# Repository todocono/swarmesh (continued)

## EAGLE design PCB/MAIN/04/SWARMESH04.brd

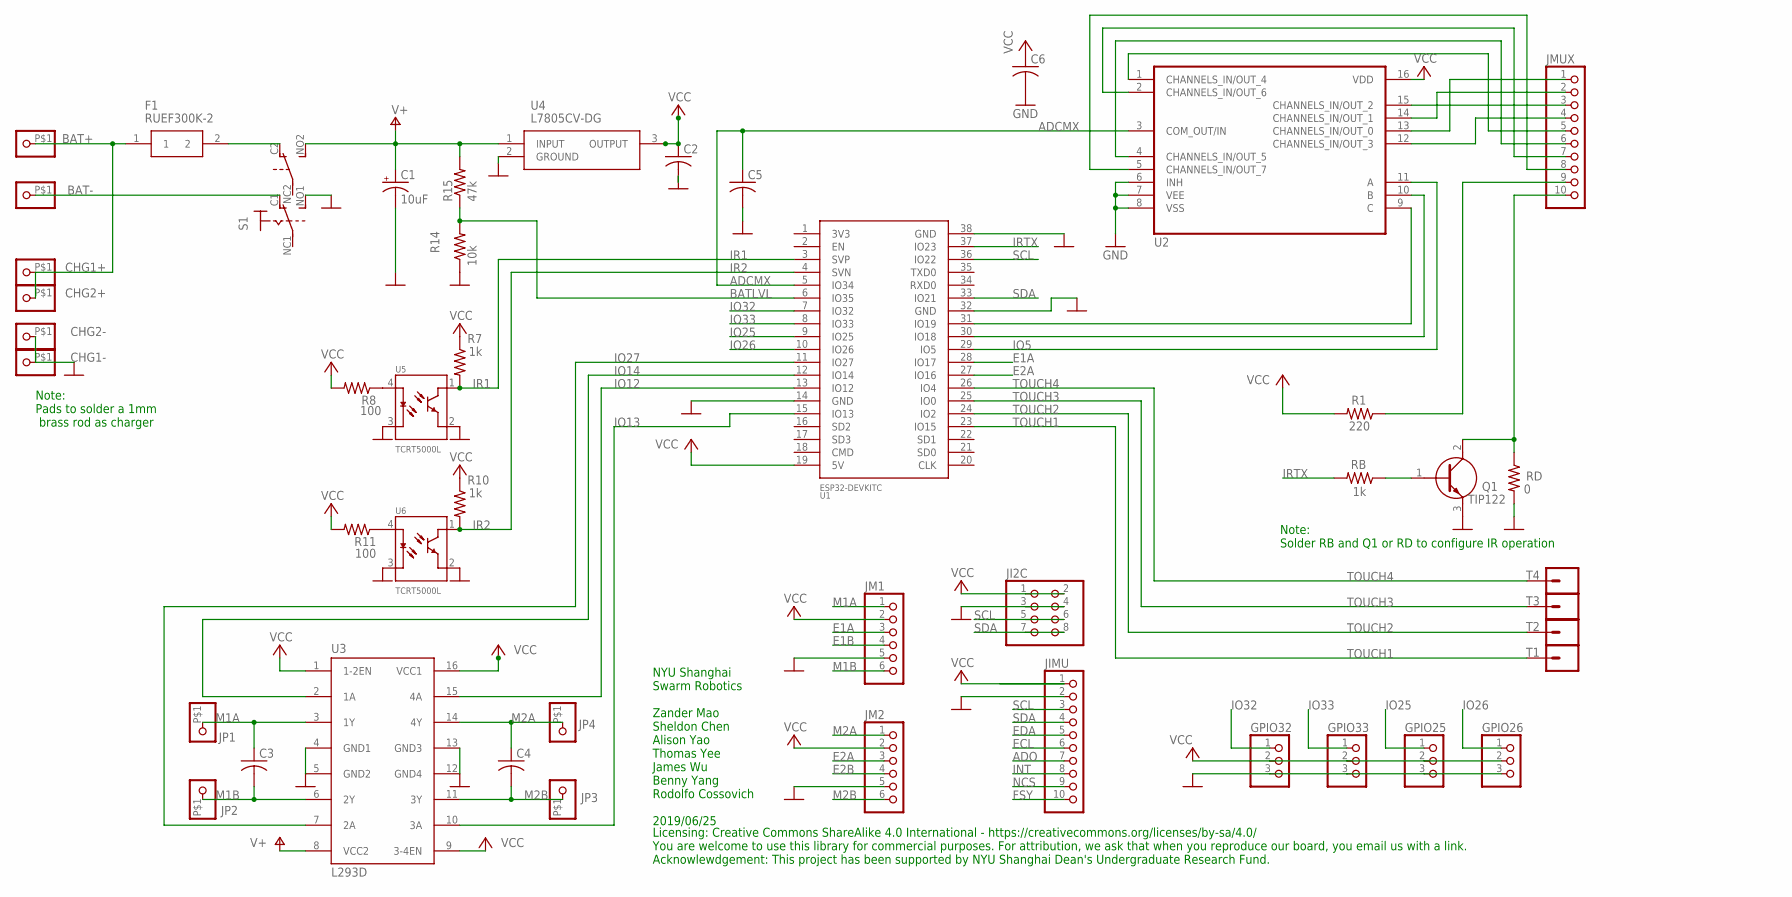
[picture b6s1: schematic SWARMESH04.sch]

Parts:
BAT+: PINHD-1X1-BIGPOGO; 1X1-BIGPOGO
BAT-: PINHD-1X1-BIGPOGO; 1X1-BIGPOGO
C1: 10uF; E2-5
C2, C5: C-US025-030X050; C025-030X050
C3, C4, C6: C-US025-025X050; C025-025X050
CHG1+, CHG1-, CHG2+, CHG2-: PINHD-1X1-BIGPOGO; 1X1-BIGPOGO
F1: RUEF300K-2; RUEF300K2
GPIO25, GPIO26, GPIO32, GPIO33: PINHD-1X3; 1X03
JI2C: PINHD-2X4; 2X04
JIMU: PINHD-1X10; 1X10-BIG
JM1, JM2: PINHD-1X6; 1X06
JMUX: PINHD-1X10; 1X10-BIG
JP1, JP2, JP3, JP4: PINHD-1X1-BIGPOGO; 1X1-BIGPOGO
Q1: TIP122; TO270P460X1020X2008-3P
R1: 220; 0207/9
R7, R10: 1k; 0207/9
R8, R11: 100; 0207/9
R14: 10k; 0207/9
R15: 47k; 0207/9
RB: 1k; 0207/9
RD: 0; 0207/9
S1: SWITCH_320-938; PS22F03
T1, T2, T3, T4: CONN_01SPRING-CONN; SPRING-CONNECTOR
U1: ESP32DEVKITC; ESP32-DEVKITC
U2: CD4051BEE4; CD4051BEE4DIP
U3: L293D; DIL16
U4: L7805CV-DG; TO270P460X1020X2008-3P
U5, U6: TCRT5000L; XDCR_TCRT5000L

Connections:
ADCMX: C5.1, U1.5 (IO34), U2.3 (COM_OUT/IN)
ADO: JIMU.7
BATLVL: R14.2, R15.1, U1.6 (IO35)
E1A: JM1.3, U1.28 (IO17)
E1B: JM1.4
E2A: JM2.3, U1.27 (IO16)
E2B: JM2.4
ECL: JIMU.6
EDA: JIMU.5
FSY: JIMU.10
GND: C1.-, C2.2, C5.2, C6.2, CHG1-.P$1, CHG2-.P$1, GPIO25.3, GPIO26.3, GPIO32.3, GPIO33.3, JI2C.3, JI2C.4, JIMU.2, JM1.5, JM2.5, Q1.3 (E), R14.1, RD.2, S1.NO1 (S), U1.14 (GND), U1.32 (GND), U1.38 (GND), U2.6 (INH), U2.7 (VEE), U2.8 (VSS), U3.4 (GND1), U3.5 (GND2), U3.12 (GND4), U3.13 (GND3), U4.2 (GROUND), U5.2 (E), U5.3 (C), U6.2 (E), U6.3 (C)
INT: JIMU.8
IO5: U1.29 (IO5), U2.11 (A)
IO12: U1.13 (IO12), U3.15 (4A)
IO13: U1.15 (IO13), U3.10 (3A)
IO14: U1.12 (IO14), U3.2 (1A)
IO25: GPIO25.1, U1.9 (IO25)
IO26: GPIO26.1, U1.10 (IO26)
IO27: U1.11 (IO27), U3.7 (2A)
IO32: GPIO32.1, U1.7 (IO32)
IO33: GPIO33.1, U1.8 (IO33)
IR1: R7.2, U1.3 (SVP), U5.1 (CO)
IR2: R10.2, U1.4 (SVN), U6.1 (CO)
IRTX: RB.2, U1.37 (IO23)
M1A: C3.1, JM1.1, JP1.P$1, U3.3 (1Y)
M1B: C3.2, JM1.6, JP2.P$1, U3.6 (2Y)
M2A: C4.1, JM2.1, JP4.P$1, U3.14 (4Y)
M2B: C4.2, JM2.6, JP3.P$1, U3.11 (3Y)
unnamed: Q1.1 (B), RB.1
unnamed: F1.2, S1.C2 (O)
unnamed: BAT-.P$1, S1.C1 (O)
unnamed: JMUX.6, U2.4 (CHANNELS_IN/OUT_5)
unnamed: U1.30 (IO18), U2.10 (B)
unnamed: U1.31 (IO19), U2.9 (C)
unnamed: R11.1, U6.4 (A)
unnamed: R8.1, U5.4 (A)
unnamed: JMUX.5, U2.1 (CHANNELS_IN/OUT_4)
unnamed: JMUX.7, U2.2 (CHANNELS_IN/OUT_6)
unnamed: JMUX.8, U2.5 (CHANNELS_IN/OUT_7)
unnamed: BAT+.P$1, CHG1+.P$1, CHG2+.P$1, F1.1
unnamed: JMUX.9, R1.1
unnamed: JMUX.10, Q1.2 (C), RD.1
unnamed: JMUX.1, U2.13 (CHANNELS_IN/OUT_0)
unnamed: JMUX.2, U2.14 (CHANNELS_IN/OUT_1)
unnamed: JMUX.4, U2.12 (CHANNELS_IN/OUT_3)
unnamed: JMUX.3, U2.15 (CHANNELS_IN/OUT_2)
NCS: JIMU.9
SCL: JI2C.5, JI2C.6, JIMU.3, U1.36 (IO22)
SDA: JI2C.7, JI2C.8, JIMU.4, U1.33 (IO21)
TOUCH1: T1.P$2, U1.23 (IO15)
TOUCH2: T2.P$2, U1.24 (IO2)
TOUCH3: T3.P$2, U1.25 (IO0)
TOUCH4: T4.P$2, U1.26 (IO4)
V+: C1.+, R15.2, S1.NO2 (S), U3.8 (VCC2), U4.1 (INPUT)
VCC: C2.1, C6.1, GPIO25.2, GPIO26.2, GPIO32.2, GPIO33.2, JI2C.1, JI2C.2, JIMU.1, JM1.2, JM2.2, R1.2, R7.1, R8.2, R10.1, R11.2, U1.19 (5V), U2.16 (VDD), U3.1 (1-2EN), U3.9 (3-4EN), U3.16 (VCC1), U4.3 (OUTPUT)

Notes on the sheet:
NYU Shanghai Swarm Robotics Zander Mao Sheldon Chen Alison Yao Thomas Yee James Wu Benny Yang Rodolfo Cossovich 2019/06/25
Licensing: Creative Commons ShareAlike 4.0 International - https://creativecommons.org/licenses/by-sa/4.0/ You are welcome to use this library for commercial purposes. For attribution, we ask that when you reproduce our board, you email us with a link. Acknowlewdgement: This project has been suppor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
Note: Solder RB and Q1 or RD to configure IR operation
Note: Pads to solder a 1mm brass rod as charger

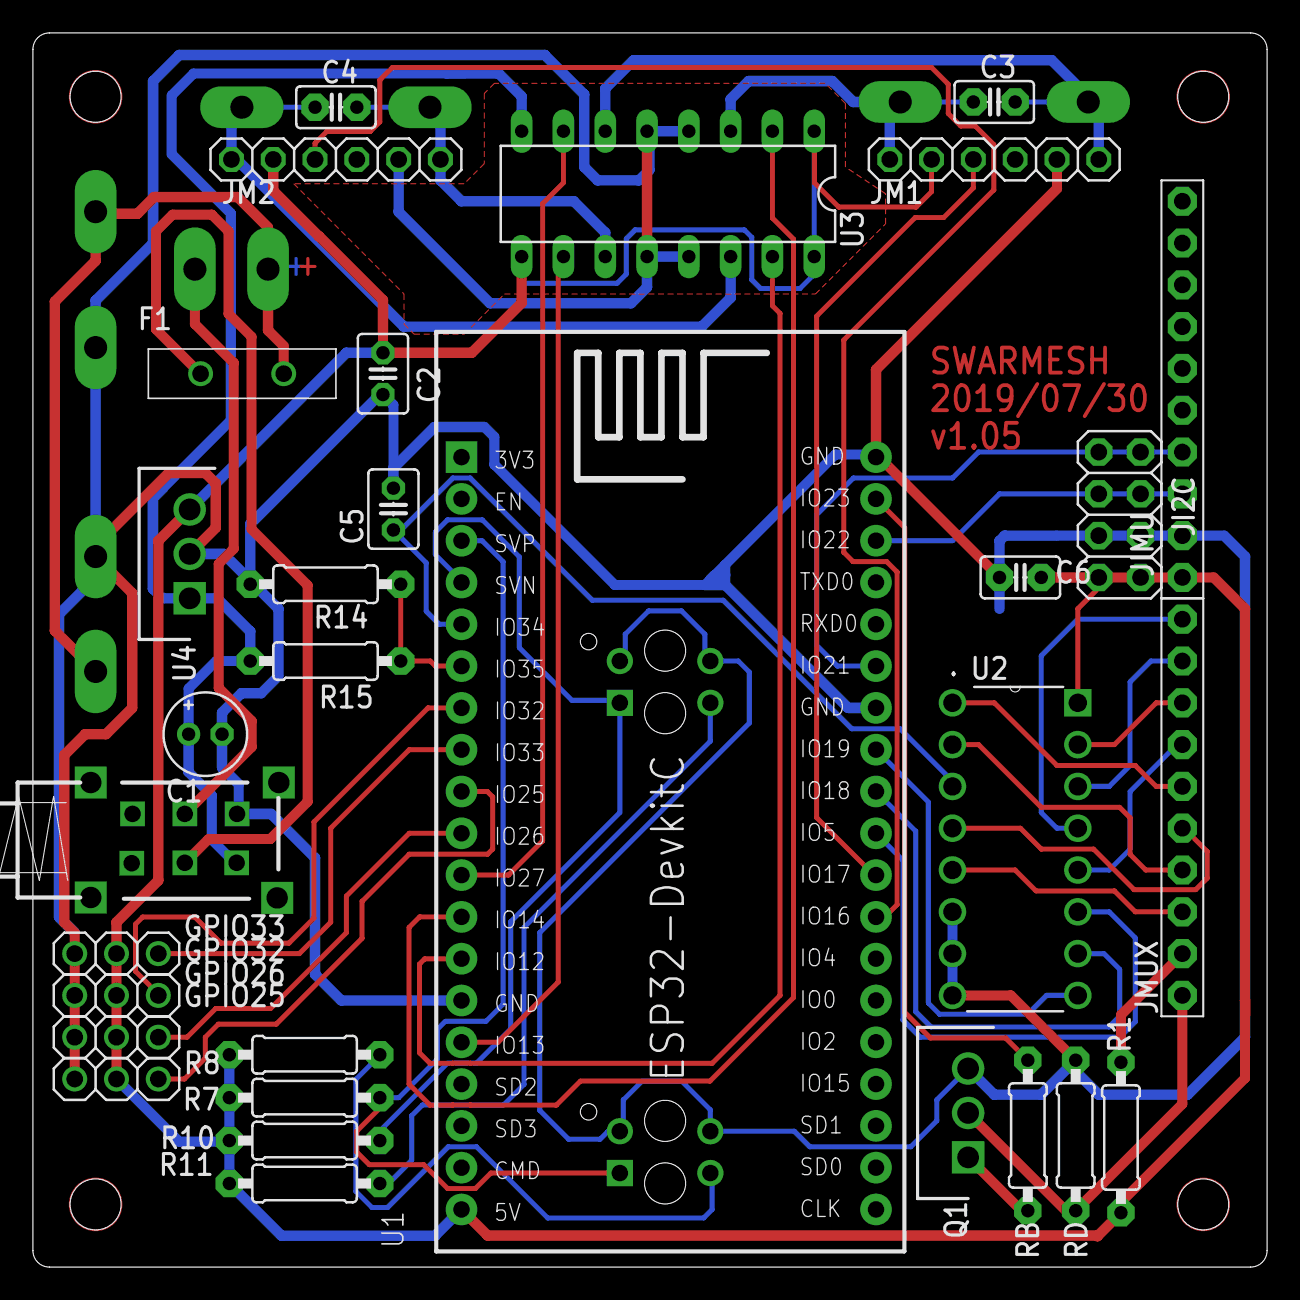
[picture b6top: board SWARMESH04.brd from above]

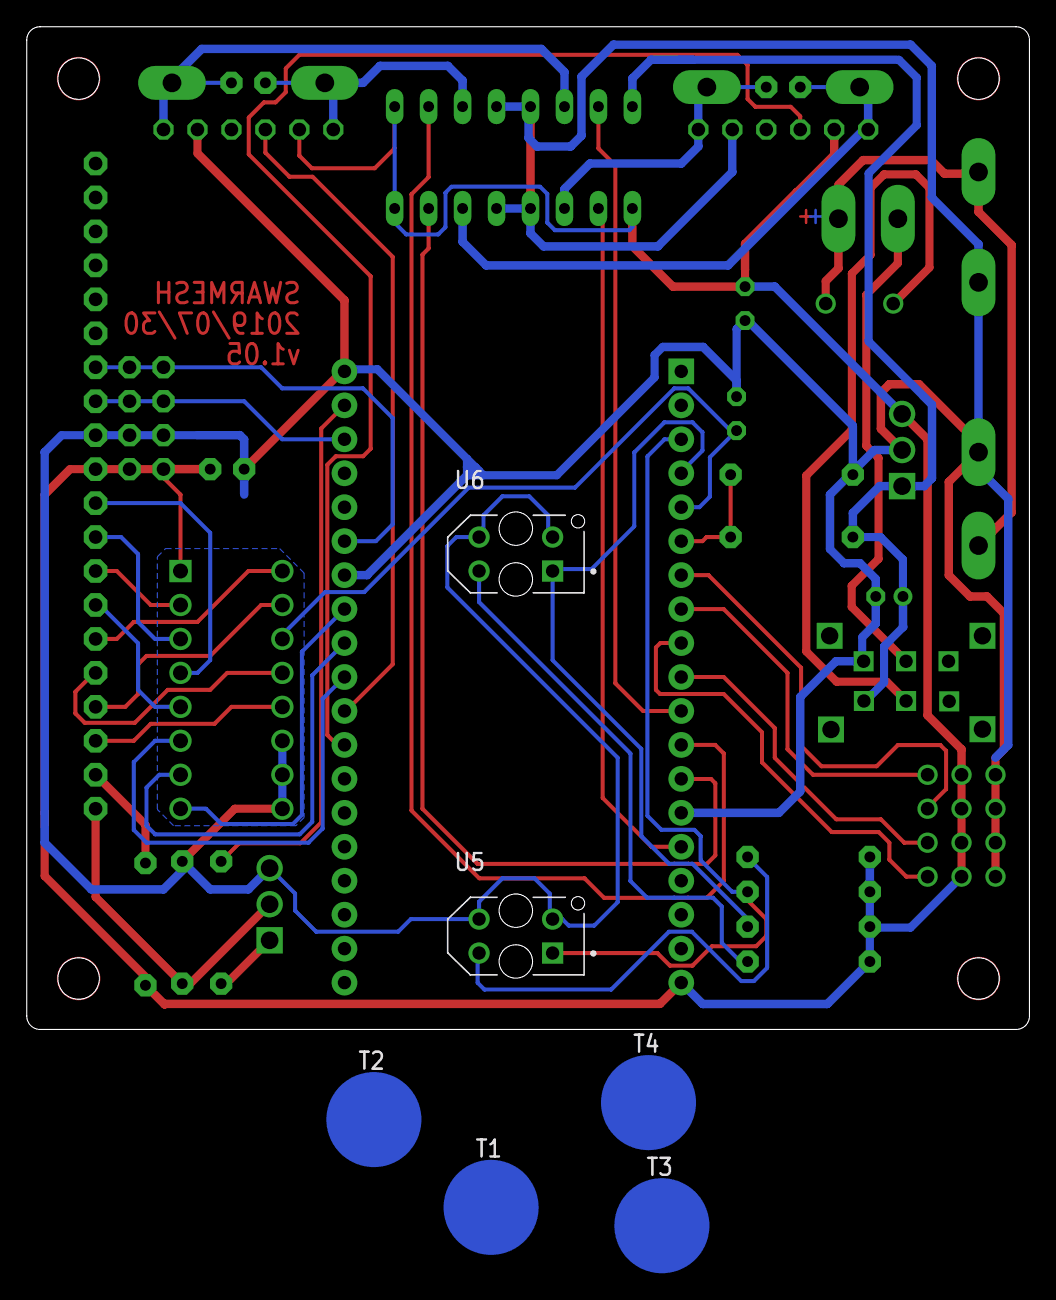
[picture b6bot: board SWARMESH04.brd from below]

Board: 2 copper layers, 75.0 x 75.0 mm, 47 parts (7 on the bottom side), 47 nets.

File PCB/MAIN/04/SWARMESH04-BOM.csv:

"Part";"Value";"Device";"Package";"Description";"ALLIED_NUMBER";"ALLIED_PRICE-STOCK";"AVAILABILITY";"DESCRIPTION";"HEIGHT";"MANUFACTURER_NAME";"MANUFACTURER_PART_NUMBER";"MF";"MOUSER_PART_NUMBER";"MOUSER_PRICE-STOCK";"MP";"MPN";"OC_FARNELL";"OC_NEWARK";"PACKAGE";"PRICE";"RS_PART_NUMBER";"RS_PRICE-STOCK";"SF_ID";
"BAT+";"";"PINHD-1X1-BIGPOGO";"1X1-BIGPOGO";"Pin header 1x1 for 0.1" spacing";"";"";"";"";"";"";"";"";"";"";"";"";"";"";"";"";"";"";"";
"BAT-";"";"PINHD-1X1-BIGPOGO";"1X1-BIGPOGO";"Pin header 1x1 for 0.1" spacing";"";"";"";"";"";"";"";"";"";"";"";"";"";"";"";"";"";"";"";
"C1";"10uF";"CPOL-USE2-5";"E2-5";"POLARIZED CAPACITOR, American symbol";"";"";"";"";"";"";"";"";"";"";"";"";"";"";"";"";"";"";"";
"C2";"";"C-US025-030X050";"C025-030X050";"CAPACITOR, American symbol";"";"";"";"";"";"";"";"";"";"";"";"";"";"";"";"";"";"";"";
"C3";"";"C-US025-025X050";"C025-025X050";"CAPACITOR, American symbol";"";"";"";"";"";"";"";"";"";"";"";"";"";"";"";"";"";"";"";
"C4";"";"C-US025-025X050";"C025-025X050";"CAPACITOR, American symbol";"";"";"";"";"";"";"";"";"";"";"";"";"";"";"";"";"";"";"";
"C5";"";"C-US025-030X050";"C025-030X050";"CAPACITOR, American symbol";"";"";"";"";"";"";"";"";"";"";"";"";"";"";"";"";"";"";"";
"C6";"";"C-US025-025X050";"C025-025X050";"CAPACITOR, American symbol";"";"";"";"";"";"";"";"";"";"";"";"";"";"";"";"";"";"";"";
"CHG1+";"";"PINHD-1X1-BIGPOGO";"1X1-BIGPOGO";"Pin header 1x1 for 0.1" spacing";"";"";"";"";"";"";"";"";"";"";"";"";"";"";"";"";"";"";"";
"CHG1-";"";"PINHD-1X1-BIGPOGO";"1X1-BIGPOGO";"Pin header 1x1 for 0.1" spacing";"";"";"";"";"";"";"";"";"";"";"";"";"";"";"";"";"";"";"";
"CHG2+";"";"PINHD-1X1-BIGPOGO";"1X1-BIGPOGO";"Pin header 1x1 for 0.1" spacing";"";"";"";"";"";"";"";"";"";"";"";"";"";"";"";"";"";"";"";
"CHG2-";"";"PINHD-1X1-BIGPOGO";"1X1-BIGPOGO";"Pin header 1x1 for 0.1" spacing";"";"";"";"";"";"";"";"";"";"";"";"";"";"";"";"";"";"";"";
"F1";"RUEF300K-2";"RUEF300K-2";"RUEF300K2";"TE CONNECTIVITY / RAYCHEM - RUEF300K-2 - RESETTABLE FUSE, PTC, 30V, 3A, RADIAL";"";"";"";"TE CONNECTIVITY / RAYCHEM - RUEF300K-2 - RESETTABLE FUSE, PTC, 30V, 3A, RADIAL";"16.5mm";"TE CONNECTIVITY / RAYCHEM";"RUEF300K-2";"";"";"";"";"";"";"";"";"";"";"";"";
"GPIO25";"";"PINHD-1X3";"1X03";"PIN HEADER";"";"";"";"";"";"";"";"";"";"";"";"";"";"";"";"";"";"";"";
"GPIO26";"";"PINHD-1X3";"1X03";"PIN HEADER";"";"";"";"";"";"";"";"";"";"";"";"";"";"";"";"";"";"";"";
"GPIO32";"";"PINHD-1X3";"1X03";"PIN HEADER";"";"";"";"";"";"";"";"";"";"";"";"";"";"";"";"";"";"";"";
"GPIO33";"";"PINHD-1X3";"1X03";"PIN HEADER";"";"";"";"";"";"";"";"";"";"";"";"";"";"";"";"";"";"";"";
"JI2C";"";"PINHD-2X4";"2X04";"PIN HEADER";"";"";"";"";"";"";"";"";"";"";"";"";"";"";"";"";"";"";"";
"JIMU";"PINHD-1X10";"PINHD-1X10";"1X10-BIG";"Pin header 1x10 0.1" spacing";"";"";"";"";"";"";"";"";"";"";"";"";"";"";"";"";"";"";"";
"JM1";"";"PINHD-1X6";"1X06";"PIN HEADER";"";"";"";"";"";"";"";"";"";"";"";"";"";"";"";"";"";"";"";
"JM2";"";"PINHD-1X6";"1X06";"PIN HEADER";"";"";"";"";"";"";"";"";"";"";"";"";"";"";"";"";"";"";"";
"JMUX";"PINHD-1X10";"PINHD-1X10";"1X10-BIG";"Pin header 1x10 0.1" spacing";"";"";"";"";"";"";"";"";"";"";"";"";"";"";"";"";"";"";"";
"JP1";"";"PINHD-1X1-BIGPOGO";"1X1-BIGPOGO";"Pin header 1x1 for 0.1" spacing";"";"";"";"";"";"";"";"";"";"";"";"";"";"";"";"";"";"";"";
"JP2";"";"PINHD-1X1-BIGPOGO";"1X1-BIGPOGO";"Pin header 1x1 for 0.1" spacing";"";"";"";"";"";"";"";"";"";"";"";"";"";"";"";"";"";"";"";
"JP3";"";"PINHD-1X1-BIGPOGO";"1X1-BIGPOGO";"Pin header 1x1 for 0.1" spacing";"";"";"";"";"";"";"";"";"";"";"";"";"";"";"";"";"";"";"";
"JP4";"";"PINHD-1X1-BIGPOGO";"1X1-BIGPOGO";"Pin header 1x1 for 0.1" spacing";"";"";"";"";"";"";"";"";"";"";"";"";"";"";"";"";"";"";"";
"Q1";"TIP122";"TIP122";"TO270P460X1020X2008-3P";"TIP122, Darlington Transistor, NPN 8 A 100 V HFE:1000, 3-Pin, TO-220";"";"";"";"TIP122, Darlington Transistor, NPN 8 A 100 V HFE:1000, 3-Pin, TO-220";"4.6mm";"STMicroelectronics";"TIP122";"";"511-TIP122";"https://www.mouser.com/Search/Refine.aspx?Keyword=511-TIP122";"";"";"";"";"";"";"";"";"";
"R1";"220";"R-US_0207/9";"0207/9";"RESISTOR, American symbol";"";"";"";"";"";"";"";"";"";"";"";"";"";"";"";"";"";"";"";
"R7";"1k";"R-US_0207/9";"0207/9";"RESISTOR, American symbol";"";"";"";"";"";"";"";"";"";"";"";"";"";"";"";"";"";"";"";
"R8";"100";"R-US_0207/9";"0207/9";"RESISTOR, American symbol";"";"";"";"";"";"";"";"";"";"";"";"";"";"";"";"";"";"";"";
"R10";"1k";"R-US_0207/9";"0207/9";"RESISTOR, American symbol";"";"";"";"";"";"";"";"";"";"";"";"";"";"";"";"";"";"";"";
"R11";"100";"R-US_0207/9";"0207/9";"RESISTOR, American symbol";"";"";"";"";"";"";"";"";"";"";"";"";"";"";"";"";"";"";"";
"R14";"10k";"R-US_0207/9";"0207/9";"RESISTOR, American symbol";"";"";"";"";"";"";"";"";"";"";"";"";"";"";"";"";"";"";"";
"R15";"47k";"R-US_0207/9";"0207/9";"RESISTOR, American symbol";"";"";"";"";"";"";"";"";"";"";"";"";"";"";"";"";"";"";"";
"RB";"1k";"R-US_0207/9";"0207/9";"RESISTOR, American symbol";"";"";"";"";"";"";"";"";"";"";"";"";"";"";"";"";"";"";"";
"RD";"0";"R-US_0207/9";"0207/9";"RESISTOR, American symbol";"";"";"";"";"";"";"";"";"";"";"";"";"";"";"";"";"";"";"";
"S1";"";"SWITCH_320-938";"PS22F03";"TOGGLE SWITCH";"";"";"";"";"";"";"";"";"";"";"";"";"";"";"";"";"";"";"";
"T1";"";"CONN_01SPRING-CONN";"SPRING-CONNECTOR";"Single connection point. Often used as Generic Header-pin footprint for 0.1 inch spaced/style header connections";"";"";"";"";"";"";"";"";"";"";"";"";"";"";"";"";"";"";"PRT-11822";
"T2";"";"CONN_01SPRING-CONN";"SPRING-CONNECTOR";"Single connection point. Often used as Generic Header-pin footprint for 0.1 inch spaced/style header connections";"";"";"";"";"";"";"";"";"";"";"";"";"";"";"";"";"";"";"PRT-11822";
"T3";"";"CONN_01SPRING-CONN";"SPRING-CONNECTOR";"Single connection point. Often used as Generic Header-pin footprint for 0.1 inch spaced/style header connections";"";"";"";"";"";"";"";"";"";"";"";"";"";"";"";"";"";"";"PRT-11822";
"T4";"";"CONN_01SPRING-CONN";"SPRING-CONNECTOR";"Single connection point. Often used as Generic Header-pin footprint for 0.1 inch spaced/style header connections";"";"";"";"";"";"";"";"";"";"";"";"";"";"";"";"";"";"";"PRT-11822";
"U1";"ESP32DEVKITC";"ESP32DEVKITC";"ESP32-DEVKITC";"";"";"";"";"";"";"";"";"";"";"";"";"";"";"";"";"";"";"";"";
"U2";"CD4051BEE4";"CD4051BEE4";"CD4051BEE4DIP";"Multiplexer 8pin ADC/DAC";"";"";"";"";"";"";"";"";"";"";"";"";"";"";"";"";"";"";"";
"U3";"L293D";"L293D";"DIL16";"PUSH-PULL 4 CHANNEL DRIVER";"";"";"";"";"";"";"";"";"";"";"";"L293D";"9589619";"56P8249";"";"";"";"";"";
"U4";"L7805CV-DG";"L7805CV-DG";"TO270P460X1020X2008-3P";"Voltage Regulator 5V 4% 1.5A TO220 L7805CV-DG, Linear Voltage Regulator, Current Limit, Shut-Down 1.5A 5 V, 3-Pin TO220";"70390055";"http://www.alliedelec.com/stmicroelectronics-l7805cv-dg/70390055/";"";"Voltage Regulator 5V 4% 1.5A TO220 L7805CV-DG, Linear Voltage Regulator, Current Limit, Shut-Down 1.5A 5 V, 3-Pin TO220";"4.6mm";"STMicroelectronics";"L7805CV-DG";"";"511-L7805CV-DG";"https://www.mouser.com/Search/Refine.aspx?Keyword=511-L7805CV-DG";"";"";"";"";"";"";"7931346P";"http://uk.rs-online.com/web/p/products/7931346P";"";
"U5";"TCRT5000L";"TCRT5000L";"XDCR_TCRT5000L";"TCRT5000 Series 940 nm 100 mA 60 mA Transistor Output Reflective Optical Sensor";"";"";"Unavailable";" TCRT5000 Series 940 nm 100 mA 60 mA Transistor Output Reflective Optical Sensor ";"";"";"";"Vishay Semiconductor";"";"";"TCRT5000L";"";"";"";"PCB Mount Vishay";"None";"";"";"";
"U6";"TCRT5000L";"TCRT5000L";"XDCR_TCRT5000L";"TCRT5000 Series 940 nm 100 mA 60 mA Transistor Output Reflective Optical Sensor";"";"";"Unavailable";" TCRT5000 Series 940 nm 100 mA 60 mA Transistor Output Reflective Optical Sensor ";"";"";"";"Vishay Semiconductor";"";"";"TCRT5000L";"";"";"";"PCB Mount Vishay";"None";"";"";"";

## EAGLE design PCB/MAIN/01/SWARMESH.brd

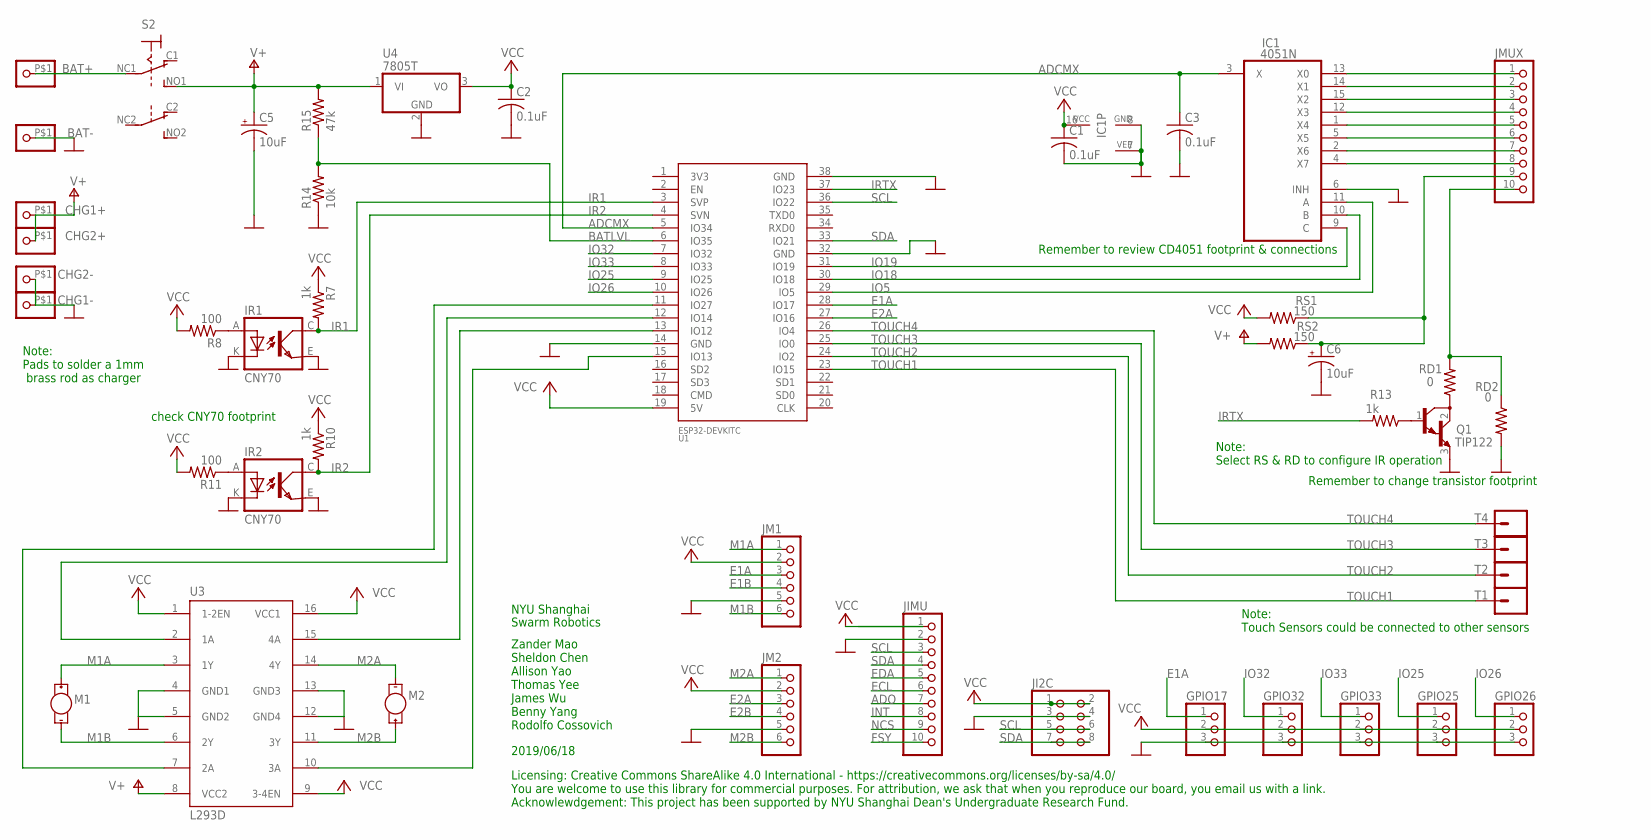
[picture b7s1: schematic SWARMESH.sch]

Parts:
BAT+: PINHD-1X1-BIGPOGO; 1X1-BIGPOGO
BAT-: PINHD-1X1-BIGPOGO; 1X1-BIGPOGO
C1, C2, C3: 0.1uF; C050-024X044
C5, C6: 10uF; E2,5-7
CHG1+, CHG1-, CHG2+, CHG2-: PINHD-1X1-BIGPOGO; 1X1-BIGPOGO
GPIO17, GPIO25, GPIO26, GPIO32, GPIO33: PINHD-1X3; 1X03
IC1: 4051N; DIL16
IR1, IR2: CNY70; 4
JI2C: PINHD-2X4; 2X04
JIMU: PINHD-1X10; 1X10-BIG
JM1, JM2: PINHD-1X6; 1X06
JMUX: PINHD-1X10; 1X10-BIG
M1, M2: MOTOR10MM; VIBE-MOTOR-10MM
Q1: TIP122; TO220
R7, R10, R13: 1k; 0207/12
R8, R11: 100; 0207/12
R14: 10k; 0207/12
R15: 47k; 0207/12
RD1, RD2: 0; 0207/12
RS1, RS2: 150; 0207/12
S2: SWITCH_320-938; PS22F03
T1, T2, T3, T4: CONN_01SPRING-CONN; SPRING-CONNECTOR
U1: ESP32DEVKITC; ESP32-DEVKITC
U3: L293D; DIL16
U4: 7805T; TO220H

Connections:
ADCMX: C3.1, IC1.3 (X), U1.5 (IO34)
ADO: JIMU.7
BATLVL: R14.2, R15.1, U1.6 (IO35)
E1A: GPIO17.1, JM1.3, U1.28 (IO17)
E1B: JM1.4
E2A: JM2.3, U1.27 (IO16)
E2B: JM2.4
ECL: JIMU.6
EDA: JIMU.5
FSY: JIMU.10
GND: BAT-.P$1, C1.2, C2.2, C3.2, C5.-, C6.-, CHG1-.P$1, CHG2-.P$1, GPIO17.3, GPIO25.3, GPIO26.3, GPIO32.3, GPIO33.3, IC1.6 (INH), IC1.7 (VEE), IC1.8 (GND), IR1.E (EMI), IR1.K (C), IR2.E (EMI), IR2.K (C), JI2C.3, JI2C.4, JIMU.2, JM1.5, JM2.5, Q1.3 (E), R14.1, RD2.2, U1.14 (GND), U1.32 (GND), U1.38 (GND), U3.4 (GND1), U3.5 (GND2), U3.12 (GND4), U3.13 (GND3), U4.2 (GND)
INT: JIMU.8
IO5: IC1.11 (A), U1.11 (IO27), U1.12 (IO14), U1.13 (IO12), U1.15 (IO13), U1.29 (IO5), U3.2 (1A), U3.7 (2A), U3.10 (3A), U3.15 (4A)
IO18: IC1.10 (B), U1.30 (IO18)
IO19: IC1.9 (C), U1.31 (IO19)
IO25: GPIO25.1, U1.9 (IO25)
IO26: GPIO26.1, U1.10 (IO26)
IO32: GPIO32.1, U1.7 (IO32)
IO33: GPIO33.1, U1.8 (IO33)
IR1: IR1.C (COL), R7.2, U1.3 (SVP)
IR2: IR2.C (COL), R10.2, U1.4 (SVN)
IRTX: R13.2, U1.37 (IO23)
M1A: JM1.1, M1.+, U3.3 (1Y)
M1B: JM1.6, M1.-, U3.6 (2Y)
M2A: JM2.1, M2.-, U3.14 (4Y)
M2B: JM2.6, M2.+, U3.11 (3Y)
unnamed: Q1.1 (B), R13.1
unnamed: IC1.13 (X0), JMUX.1
unnamed: IC1.14 (X1), JMUX.2
unnamed: IC1.15 (X2), JMUX.3
unnamed: IC1.12 (X3), JMUX.4
unnamed: IC1.1 (X4), JMUX.5
unnamed: IC1.5 (X5), JMUX.6
unnamed: IC1.2 (X6), JMUX.7
unnamed: IC1.4 (X7), JMUX.8
unnamed: C6.+, JMUX.9, RS1.1, RS2.1
unnamed: JMUX.10, RD1.2, RD2.1
unnamed: IR2.A, R11.1
unnamed: BAT+.P$1, S2.NC1
unnamed: IR1.A, R8.1
unnamed: Q1.2 (C), RD1.1
NCS: JIMU.9
SCL: JI2C.5, JI2C.6, JIMU.3, U1.36 (IO22)
SDA: JI2C.7, JI2C.8, JIMU.4, U1.33 (IO21)
TOUCH1: T1.P$2, U1.23 (IO15)
TOUCH2: T2.P$2, U1.24 (IO2)
TOUCH3: T3.P$2, U1.25 (IO0)
TOUCH4: T4.P$2, U1.26 (IO4)
V+: C5.+, CHG1+.P$1, CHG2+.P$1, RS2.2, S2.NO1 (S), U3.8 (VCC2), U4.1 (VI)
VCC: C1.1, C2.1, GPIO17.2, GPIO25.2, GPIO26.2, GPIO32.2, GPIO33.2, IC1.16 (VCC), JI2C.1, JI2C.2, JIMU.1, JM1.2, JM2.2, R7.1, R8.2, R10.1, R11.2, RS1.2, U1.19 (5V), U3.1 (1-2EN), U3.9 (3-4EN), U3.16 (VCC1), U4.3 (VO)

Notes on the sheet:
Swarm Robotics
NYU Shanghai
2019/06/18
Zander Mao Sheldon Chen Allison Yao Thomas Yee James Wu Benny Yang Rodolfo Cossovich
Remember to change transistor footprint
Licensing: Creative Commons ShareAlike 4.0 International - https://creativecommons.org/licenses/by-sa/4.0/ You are welcome to use this library for commercial purposes. For attribution, we ask that when you reproduce our board, you email us with a link. Acknowlewdgement: This project has been suppor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
Remember to review CD4051 footprint & connections
Note: Select RS & RD to configure IR operation
check CNY70 footprint
Note: Pads to solder a 1mm brass rod as charger
Note: Touch Sensors could be connected to other sensors

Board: 2 copper layers, 46 parts (0 on the bottom side), 42 nets, no tracks yet.

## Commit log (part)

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2019-09-26 added Arduino examples
2019-09-26 brought old blueprints over
2019-09-26 renamed incoherent files
2019-09-26 renamed renders
2019-10-14 modified readme
2019-10-22 added turn ninety
2019-11-01 added IR location
2019-11-02 separated IR in two boards
2019-11-02 updated IRRx
2019-11-05 modified IR-TX
2019-11-08 mesh+motor code added
2019-11-08 IR+motor/transistor code
2019-11-17 demoCode written
2019-12-12 added serial
2019-12-12 added leds
2020-06-03 Aruco marker detection added
    Info returned in a dictionary containing relative position and orientation
2020-06-03 multicast tests added
    first upload the testMulticastArduino.ino in testMulticastArduino folder, then run multicast_send_test.py
2020-06-04 camera calibrated, coordinates converted to real world coordinates
2020-06-04 Send pos using multicast
2020-06-04 fixed time function
2020-06-05 test board for wireless charging and 3V motors
2020-06-05 Perpective transformation
2020-06-05 Syntax adjust
2020-06-05 Pespective transformation
2020-06-09 Adjust perspective transformation
2020-06-09 multicast motor test
2020-06-09 move fixed
2020-06-09 moving to goal enabled
2020-06-09 Direction auto-corrector added
2020-06-10 Updated arduino multicast channels
2020-06-10 functioning distributedly
2020-06-10 (test)oop file added
2020-06-11 oop added to arduino code
2020-06-11 oop working
2020-06-11 testing
2020-06-12 oop stable
2020-06-12 minor modifications to the code
2020-06-12 nothing
2020-06-12 pcb v1.0.1 with pins for sensors and other revisions
2020-06-16 FSM fulfilled
2020-06-16 locomotion library created
2020-06-17 Modularization complete
    Need to look for potential bugs (memory leak, etc.) in the future updates
2020-06-17 Simulation files
2020-06-17 Reviese driver and slave file
2020-06-18 Simulation revised( direction probelm unsolved)
2020-06-19 Simulation revision
    the first version that works !!!!!!!!
    Improvement expectation:
    1. minimize error (distance + orientation)
    2. simulate the robot better?
2020-06-19 Webots project files
2020-06-22 Update webots project file and controller code
2020-06-26 PCB v1.0.2 with ESP32 module, IR sensors, etc
2020-06-30 Updates for board v1.0.2
2020-06-30 simple PID added
2020-07-06 route setting enabled
2020-07-07 new IR testing code added
2020-07-08 Update simulation for 10 robots
2020-07-08 Destination class added to testRouting
2020-07-09 collision avoidance file created
2020-07-09 updated collision avoidance code
2020-07-10 pcb v1.0.3
2020-07-10 collision avoidance added
2020-07-10 pcb v1.0.3 updates
2020-07-13 working task allocation
2020-07-13 routing & task allocation working
    routing includes auto_routing, check_task, random path generator, etc.
2020-07-13 Add wireless charging board
2020-07-14 pid course correction added
2020-07-15 updated absolute position aquisition
2020-07-15 PID testbench established
2020-07-16 PID with camera
    (needs to adjust the pid value to make it converge faster)
2020-07-17 simulation upate (routing)
2020-07-20 pid stable
2020-07-21 PID very stable
2020-07-21 Simulation routing with PID
2020-07-22 PCB v1.0.4 Update
2020-07-23 fghj
2020-07-25 collision avoidance updated
2020-07-25 collision avoidance rules updated
2020-07-27 collision functions verified
2020-07-28 reroute sort of working
2020-07-29 fixed minor bugs
2020-07-29 front collision avoidance working, combined task assignment
2020-07-30 one-way test assignment tested okay
2020-07-30 task assignment working
2020-07-30 fixed id setup
2020-07-31 finale
2020-08-01 Picture documented, testLight created
2020-08-01 light show demo
2020-11-27 Added PDF of schematic
